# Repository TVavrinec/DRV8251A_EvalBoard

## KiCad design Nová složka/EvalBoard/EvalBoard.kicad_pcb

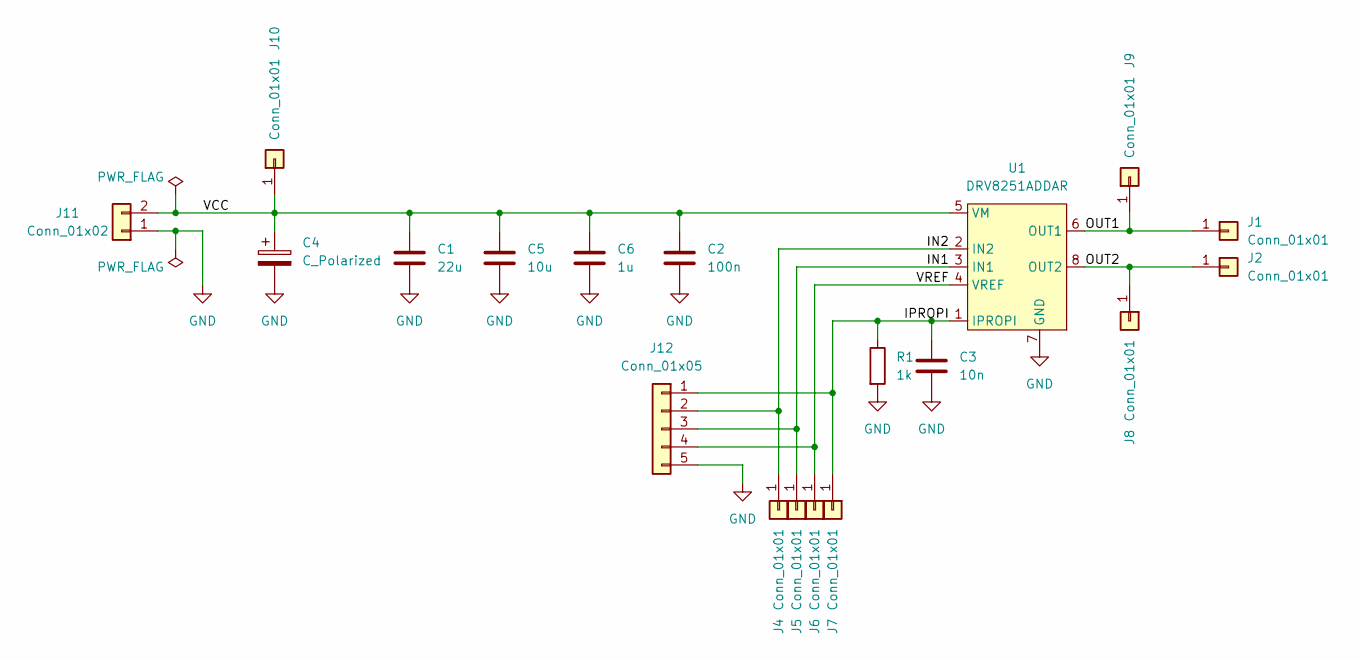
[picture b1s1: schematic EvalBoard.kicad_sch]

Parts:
C1: 22u; C_2220_5650Metric; LCSC C5156742
C2: 100n; L_0805_2012Metric
C3: 10n; C_0603_1608Metric; LCSC C15195
C4: C_Polarized; CP_Radial_D10.0mm_P5.00mm
C5: 10u; C_2220_5650Metric
C6: 1u; C_0805_2012Metric
J1, J2: Conn_01x01; TerminalBlock_MetzConnect_360271_1x01_Horizontal_ScrewM3.0_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
J4, J5, J6, J7, J8, J9, J10: Conn_01x01; PinHeader_1x01_P2.00mm_Vertical
J11: Conn_01x02; TerminalBlock_RND_205-00067_1x02_P7.50mm_Horizontal
J12: Conn_01x05; PinHeader_1x05_P2.54mm_Vertical
R1: 1k; R_0603_1608Metric; LCSC C852624
U1: DRV8251ADDAR; HSOP-8-1EP_3.9x4.9mm_P1.27mm_EP2.41x3.1mm

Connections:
/IN1: J5.1, J12.3, U1.3 (IN1)
/IN2: J4.1, J12.2, U1.2 (IN2)
/IPROPI: C3.1, J7.1, J12.1, R1.1, U1.1 (IPROPI)
/OUT1: J1.1, J9.1, U1.6 (OUT1)
/OUT2: J2.1, J8.1, U1.8 (OUT2)
/VCC: C1.1, C2.1, C4.1, C5.1, C6.1, J10.1, J11.2, U1.5 (VM)
/VREF: J6.1, J12.4, U1.4 (VREF)
GND: C1.2, C2.2, C3.2, C4.2, C5.2, C6.2, J11.1, J12.5, R1.2, U1.7 (GND), U1.9 (GND)

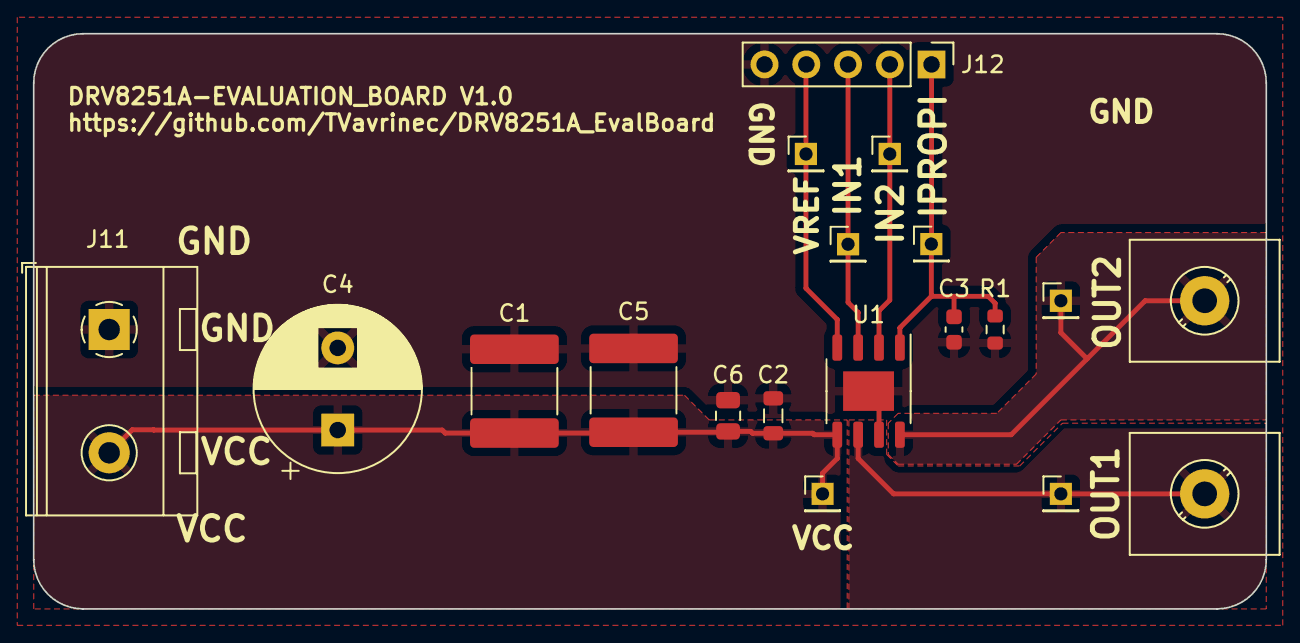
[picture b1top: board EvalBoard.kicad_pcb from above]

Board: 2 copper layers, 75.0 x 35.0 mm, 19 parts (0 on the bottom side), 8 nets.

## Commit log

2023-09-28 V1.0.0
2023-09-28 Cleaning folders
2023-09-29 Mounting holes and ground vias
2023-09-29 Margine around mounting holes
